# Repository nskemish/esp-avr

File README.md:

# Potreban alat za izradu jeste avr

Za MacOS je potrebno uraditi u terminalu

brew trust osx-cross/avr
brew install avr-gcc

'''
cat <<'EOF' > .clangd
CompileFlags:
  CompilationDatabase: /Users/ognjengutesa/Developments/espavr/build
  Remove: [-m*, -f*]
  Add:
    - -isystem/opt/homebrew/opt/avr-gcc@9/avr/include
    - -D__AVR_ATtiny85__
    - -DF_CPU=1000000UL
EOF
'''

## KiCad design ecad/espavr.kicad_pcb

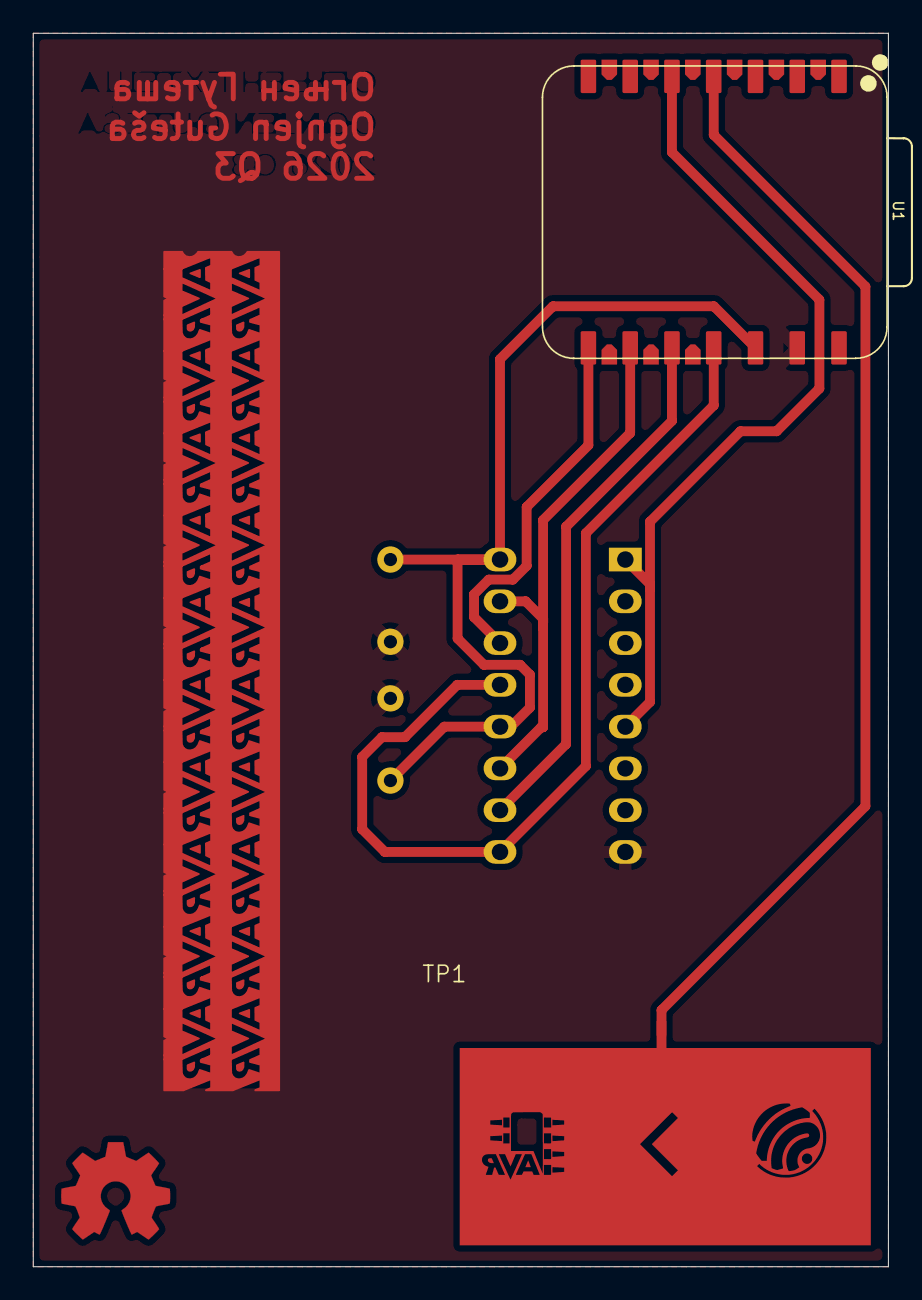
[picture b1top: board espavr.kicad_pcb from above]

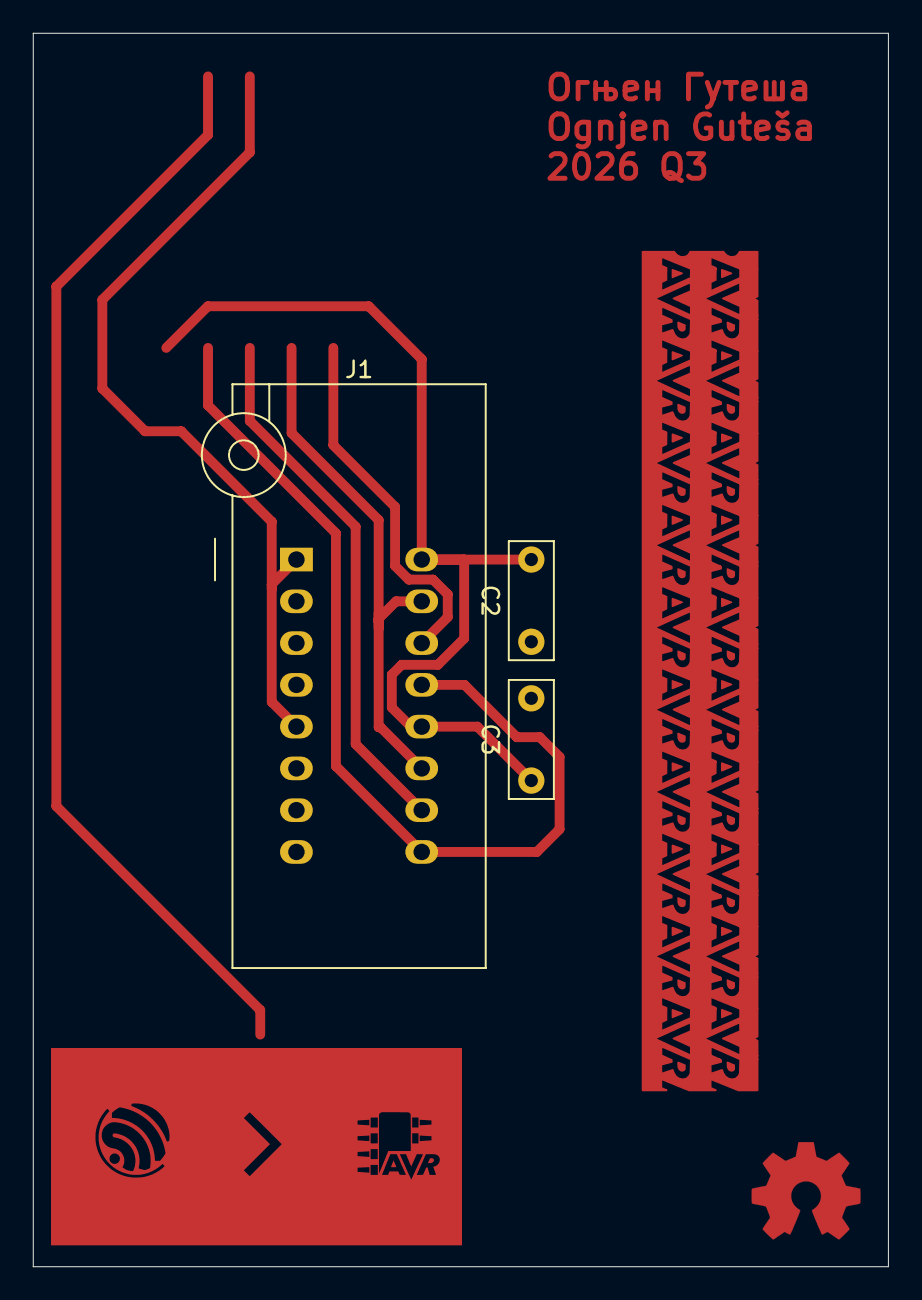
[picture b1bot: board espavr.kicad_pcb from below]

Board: 2 copper layers, 52.0 x 75.0 mm, 5 parts (3 on the bottom side), 8 nets.

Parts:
C2, C3: C; C_Rect_L7.0mm_W2.5mm_P5.00mm
J1: Conn_01x16_Pin; DIP_Socket-16_W4.3mm_W5.08mm_W7.62mm_W10.16mm_W10.9mm_3M_21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
TP1: TestPoint; FlashCAP
U1: XIAO-ESP32-S3-Plus-SMD

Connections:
+3.3V: C2.2, C3.1, J1.12, J1.16, U1.12 (VCC_3V3)
/MISO1: J1.14, U1.8 (U0RXD_D7/RX)
/MISO2: J1.10, U1.10 (GPIO8_D9/A9/MISO)
/MOSI: J1.9, J1.13, U1.11 (GPIO9_D10/A10/MOSI)
/RST: J1.1, J1.5, U1.5 (GPIO5_D4/A4/I2C_SDA)
/SCK: J1.11, J1.15, U1.9 (GPIO7_D8/A8/SCK)
GND: C2.1, C3.2, J1.4, J1.8, U1.13 (GND)
unnamed: TP1.1 (1_1), U1.4 (GPIO4_D3/A3)
